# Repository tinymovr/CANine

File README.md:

# CANine Schematics, Drawings and Firmware

## Schematics and Drawings

CANine is Certified Open Source Hardware

[OSHW] GR000007 | Certified open source hardware | oshwa.org/cert

## Firmware

USB CDC firmware for the CANine USB⟷CAN Bus adapter. This firmware is based on slcan but gets rid of the Virtual Com Port cruft, resulting in leaner communication on all platforms, and especially on Windows. Most slcan commands are the same, but the CAN frame size is fixed and data is transmitted as binary (instead of ascii in slcan).

This firmware should be compatible with CANable adapters, but has not been tested.

[Documentation](https://canine.readthedocs.io/en/latest/)

### Flashing

We now offer [a simple Web-based firmware update service](https://tinymovr.github.io/CANine/). Instructions are available on the page. Chrome and Edge are supported.

### Using

This firmware is compatible with python-can through the corresponding [plugin available on PyPi](https://pypi.org/project/python-can-canine/).

This firmware is compatible with Tinymovr. To use with Studio, add the command line parameter `--bus=canine` when launching.

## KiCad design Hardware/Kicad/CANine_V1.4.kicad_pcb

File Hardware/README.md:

# CANine CAN Adapter

This is a USB Type-C <-> CAN Bus adapter. Itself it is an adaptation of the [CANable board](https://canable.io/). It features a 2.54mm screw terminal, a 4-pin JST-GH connector, and a 2.54mm header. In addition, it features a convenient DIP switch for setting CAN termination resistor and boot mode.

This design is released under the original CANable license.

This directory also includes an STL model for a compact 3D printable case.

There is also an [alternative case design for the legacy CANine](https://github.com/ThotAlion/BLDC-design-help/tree/main/STL/USBCANBox) by ThotAlion.

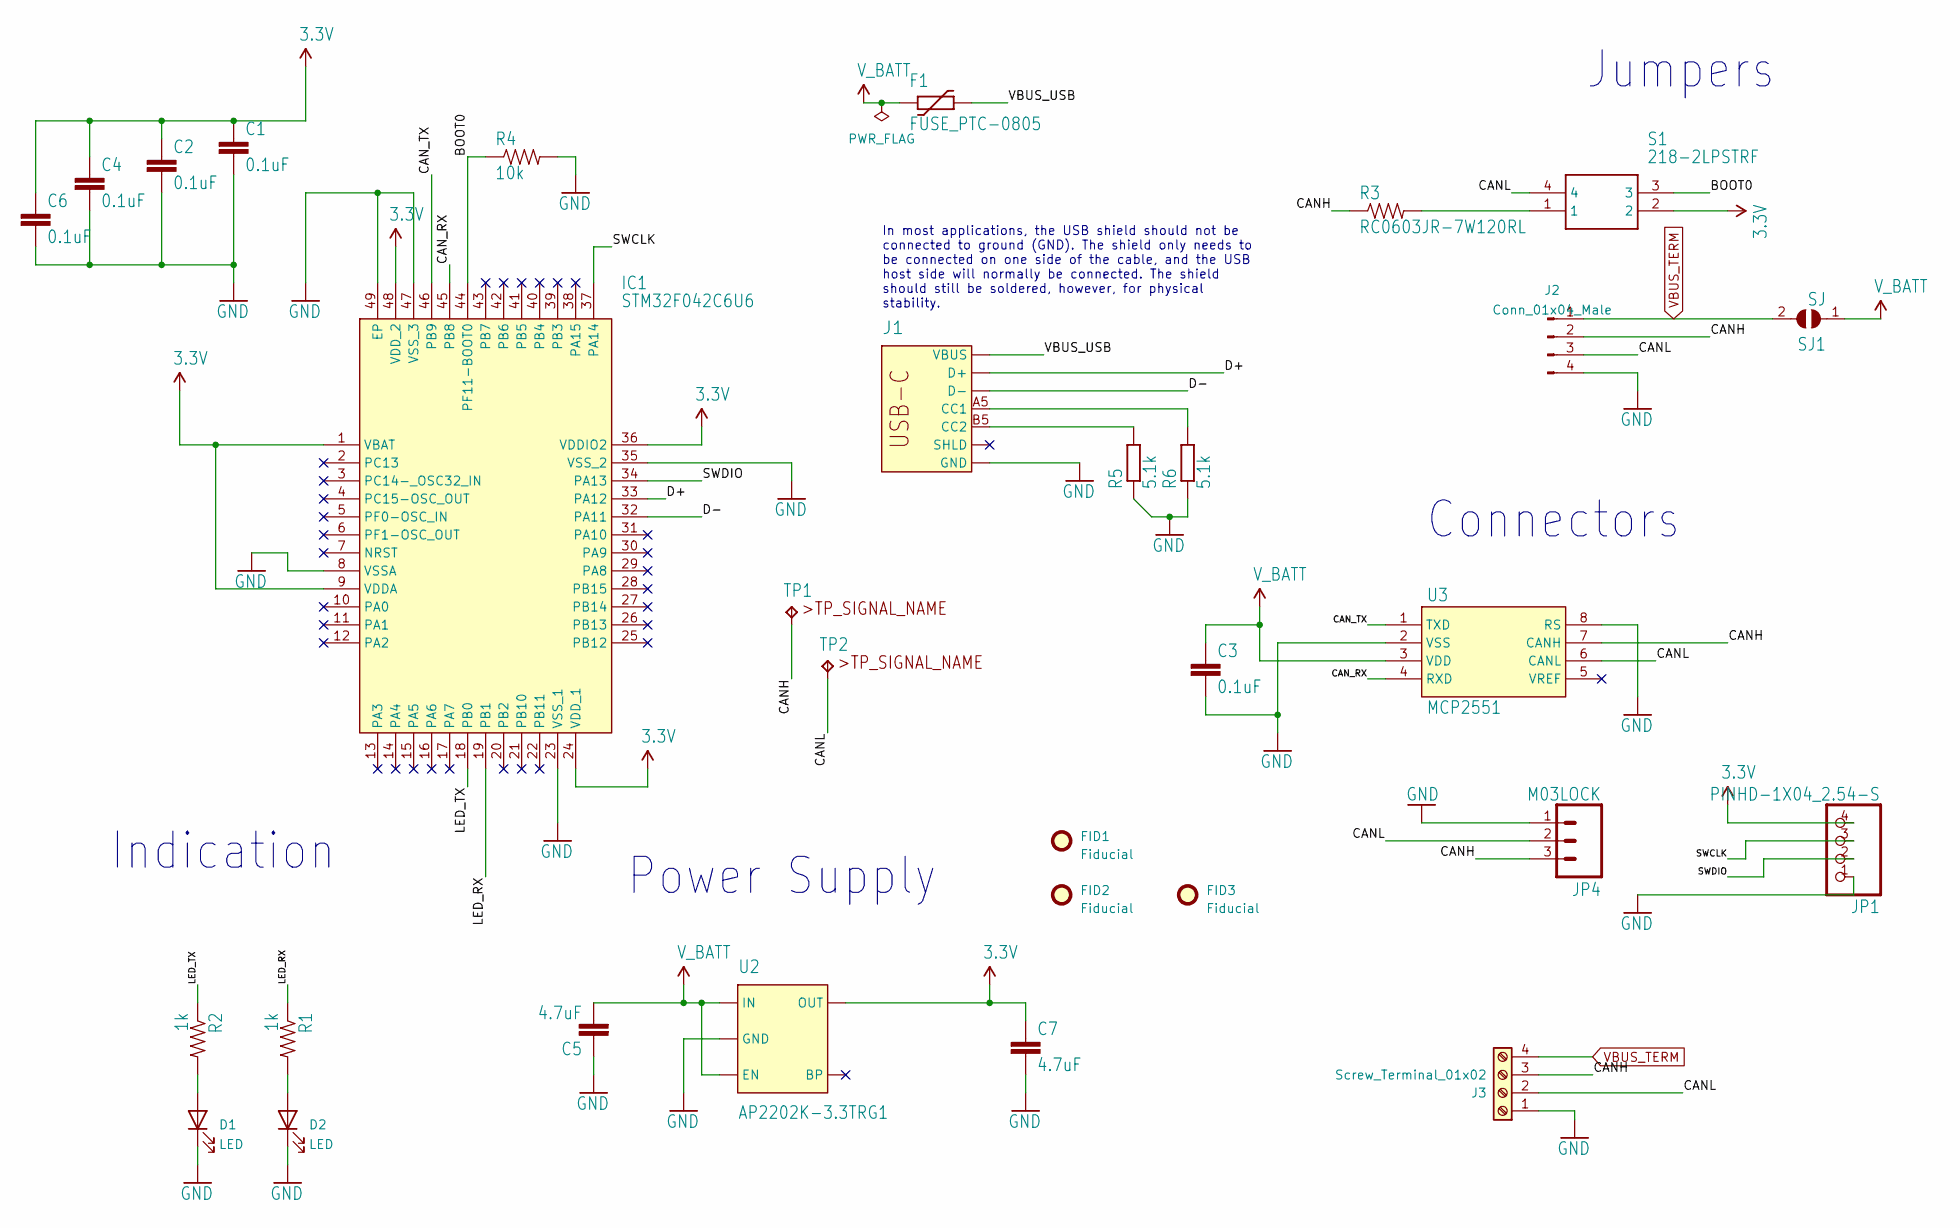
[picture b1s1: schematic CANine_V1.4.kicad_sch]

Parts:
C1, C2, C3, C4, C6: 0.1uF; C_0603_1608Metric
C5, C7: 4.7uF; C_0603_1608Metric
D1, D2: LED; LED_0603_1608Metric
F1: FUSE_PTC-0805; PTC0805
FID1, FID2, FID3: Fiducial; Fiducial_0.75mm_Mask1.5mm
IC1: STM32F042C6U6; QFN-48-1EP_7x7mm_P0.5mm_EP5.6x5.6mm
J1: SPARKFUN-CONNECTORS_USB_C16PIN; SPARKFUN-CONNECTORS_USB-C-16P
J2: Conn_01x04_Male; JST_GH_BM04B-GHS-TBT_1x04-1MP_P1.25mm_Vertical
J3: Screw_Terminal_01x02; TerminalBlock_Phoenix_MPT-0,5-4-2.54_1x04_P2.54mm_Horizontal
JP1: PINHD-1X04_2.54-S; 1X04-S
JP4: M03LOCK; 1X03_LOCK
R1, R2: 1k; R_0603_1608Metric
R3: RC0603JR-7W120RL; R_0603_1608Metric
R4: 10k; R_0603_1608Metric
R5, R6: 5.1k; R_0603_1608Metric
S1: 218-2LPSTRF; 2182LPSTRF
SJ1: SJ
TP1, TP2: TPTP16R; TP16R
U2: AP2202K-3.3TRG1; SOT-23-5
U3: MCP2551; SOIC-8_3.9x4.9mm_P1.27mm

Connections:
3.3V: C1.1, C2.1, C4.1, C6.1, C7.1, IC1.1 (VBAT), IC1.9 (VDDA), IC1.24 (VDD_1), IC1.36 (VDDIO2), IC1.48 (VDD_2), JP1.4, S1.2, U2.5 (OUT)
/BOOT0: IC1.44 (PF11-BOOT0), R4.1, S1.3
/CANH: J2.2, J3.3, JP4.3, R3.1, TP1.TP, U3.7 (CANH)
/CANL: J2.3, J3.2, JP4.2, S1.4, TP2.TP, U3.6 (CANL)
/CAN_RX: IC1.45 (PB8), U3.4 (RXD)
/CAN_TX: IC1.46 (PB9), U3.1 (TXD)
/D+: IC1.33 (PA12), J1.A6 (D+), J1.B6 (D+)
/D-: IC1.32 (PA11), J1.A7 (D-), J1.B7 (D-)
/LED_RX: IC1.19 (PB1), R1.1
/LED_TX: IC1.18 (PB0), R2.1
/SWCLK: IC1.37 (PA14), JP1.3
/SWDIO: IC1.34 (PA13), JP1.2
/VBUS_USB: F1.2, J1.VBUS1 (VBUS), J1.VBUS2 (VBUS)
GND: C1.2, C2.2, C3.2, C4.2, C5.1, C6.2, C7.2, D1.1 (K), D2.1 (K), IC1.8 (VSSA), IC1.23 (VSS_1), IC1.35 (VSS_2), IC1.47 (VSS_3), IC1.49 (EP), J1.GND, J1.GND2 (GND), J2.4, J3.1, JP1.1, JP4.1, R4.2, R5.1, R6.1, U2.2 (GND), U3.2 (VSS), U3.8 (RS)
unnamed: D1.2 (A), R2.2
unnamed: D2.2 (A), R1.2
unnamed: J1.A5 (CC1), R6.2
unnamed: J1.B5 (CC2), R5.2
unnamed: R3.2, S1.1
VBUS_TERM: J2.1, J3.4, SJ1.2
V_BATT: C3.1, C5.2, F1.1, SJ1.1, U2.1 (IN), U2.3 (EN), U3.3 (VDD)

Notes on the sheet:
Jumpers
In most applications, the USB shield should not be connected to ground (GND). The shield only needs to be connected on one side of the cable, and the USB host side will normally be connected. The shield should still be soldered, however, for physical stability.
Connectors
Indication
Power Supply

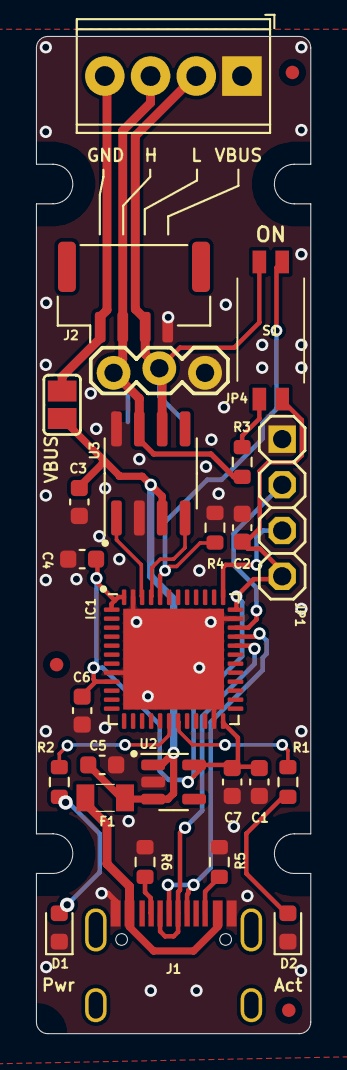
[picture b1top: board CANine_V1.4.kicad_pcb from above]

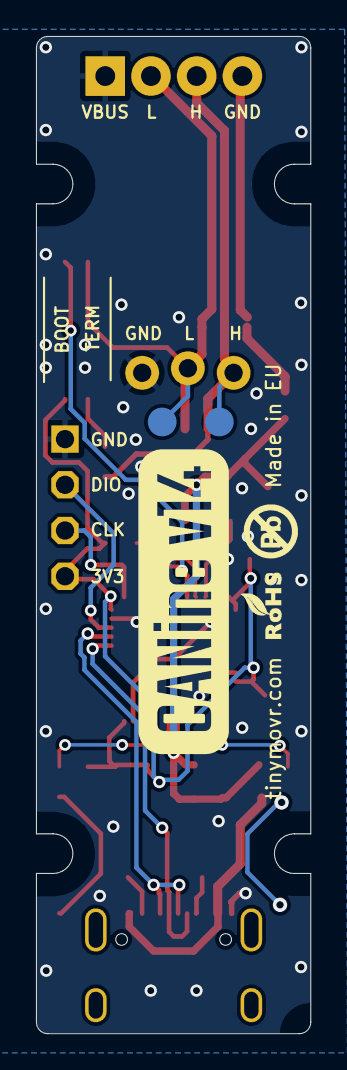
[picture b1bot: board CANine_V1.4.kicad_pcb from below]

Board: 2 copper layers, 15.2 x 55.4 mm, 31 parts (2 on the bottom side), 21 nets.

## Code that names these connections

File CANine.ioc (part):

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Mcu.UserName=STM32F042C6Tx
PA11.Mode=Device
RCC.SYSCLKSource=RCC_SYSCLKSOURCE_HSI48
PA13.Signal=SYS_SWDIO
PA12.Signal=USB_DP
PB1.GPIO_PuPd=GPIO_PULLUP
PB9.Mode=CAN_Activate
board=custom
PB0.GPIOParameters=GPIO_PuPd
PA14.Mode=Serial_Wire
PA13.Mode=Serial_Wire
Mcu.Name=STM32F042C(4-6)Tx
RCC.SYSCLKFreq_VALUE=48000000
Mcu.Package=LQFP48
PB9.Signal=CAN_TX
PB1.Signal=GPIO_Output
PA12.Mode=Device
PA11.Signal=USB_DM
PA14.Signal=SYS_SWCLK
PB8.Mode=CAN_Activate
PB8.Signal=CAN_RX
PB0.Signal=GPIO_Output
PB0.GPIO_PuPd=GPIO_PULLUP
PB1.GPIOParameters=GPIO_PuPd

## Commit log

2021-07-12 fix packet length
2021-07-12 optimize frame parsing
2021-07-13 fix buffer indices
2021-07-13 remove debug variable
2021-07-14 add build to ignore
2021-07-14 initial makefile
2021-07-14 make git version symbols available
2021-07-14 typo in symbol declaration
2021-07-15 fix indentation
2021-07-15 also build intel hex file
2021-07-15 ignore vscode settings
2021-07-16 add flashing script and instructions
2021-07-16 add windows bat script
2021-07-17 Add instructions and prompt
2021-07-17 Add curl flags
2021-07-17 Remove sudo requirement from macos
2021-07-17 Add quiet flag to wget
2021-07-18 Add vendor and device ids
2021-07-18 Add add vendor and device ids
2021-07-18 Use vendor and device ids
2021-07-18 Add vendor and device ids (#1)
    * Add vendor and device ids
    * Add add vendor and device ids
    * Use vendor and device ids
2021-07-31 migrate docs
2021-07-31 add docs link
2021-07-31 migrate hardware
2021-08-20 Update windows instructions
2022-09-13 add webdfu vanilla setup
2022-09-13 simplify page and webdfu script
2022-09-13 add style
2022-09-13 update title
2022-09-13 get file from url
2022-09-13 make fw local
2022-09-13 device connecting
2022-09-14 update working
2022-09-15 comments
2022-09-16 handle all cases
2022-09-16 clearly mark changes
2022-09-16 ignore init warning
2022-10-12 print binary data
2022-10-12 fix path
2022-10-12 remove console log
2022-10-12 Fix logging
2022-10-12 revert some breaking changes
2022-10-12 remove legacy update scripts
2022-10-12 update instructions
2022-10-23 update docs
2022-10-23 add more details to docs
2022-10-25 add additional information for windows and macos
2022-10-26 additional instructions for installing python-can
2022-10-30 update install command
2022-10-30 add latest hardware revision
2022-11-24 Create Code of Conduct (#7)
2022-11-24 Create LICENSE
2022-11-24 Create LICENSE_CANABLE
2022-11-24 Create LICENSE (#8)
    * Create LICENSE
    * Create LICENSE_CANABLE
2023-03-13 handle misses and errors in cdc transmission
2023-03-13 refactor function name
2023-04-03 Update README.md with canine python-can plugin
2023-04-03 Fix formatting
2023-04-17 update install instructions
2023-05-30 add hardware preparation for flashing
2023-08-05 add udev rule instructions
2023-12-16 update hardware files
2023-12-16 Update LICENSE
2023-12-16 Roll back LICENSE
2023-12-16 Create LICENSE for hardware
2023-12-24 ignore backups
2024-05-03 add 3D printed case diagram
2024-05-03 add readthedocs file
2024-05-03 fixed section depth
